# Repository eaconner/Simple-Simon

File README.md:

# Simple Simon Kit #

Red then green...no, blue?...wait!...BUZZ! Remember the classic game of Simon?
Well, here is a build-your-own Simon kit that will sharpen your reaction time while teaching you basic soldering (a useful skill in its own right).

After you have successfully built a working Simon game, you will have a greater knowledge of through-hole soldering and the tools, techniques, and terminology required to populate your own PCB prototype. Additionally, the source code and design files are available, making this project a great entryway into microcontrollers and embedded programming. Game on!

## Parts List ##
|	Qty	|	Part				|	Description				|	Digikey Part #	|
|:-----:|-----------------------|---------------------------|-------------------|
|	1	|	U1					|	Atmel ATtiny45			|	ATTINY45-20PU	|
|	4	|	R1, R2, R3, R4		|	470ohm 1/4w Resistor	|	CF14JT470RCT	|
|	1	|	D1					|	5mm Red LED				|	160-1678		|
|	1	|	D2					|	5mm Green LED			|	160-1677		|
|	1	|	D3					|	5mm Blue LED			|	160-1610		|
|	1	|	D4					|	5mm Yellow LED			|	160-1686		|
|	1	|	SG1					|	12mm Piezo Buzzer		|	102-3752		|
|	5	|	S1, S2, S3, S4, S5	|	Pushbutton				|	450-1644		|
|	1	|	BAT1				|	Battery Holder			|	BS-7			|
|	1	|	BAT1				|	CR2032 Battery			|	P189			|

## Instructions ##
1. Insert the ATtiny45 microcontroller into U1. Make sure the dot in the corner of the chip is aligned with the white silk screen dot on the board. Flip the board over, then solder into place.
2. Insert the (4) four resistors into R1, R2, R3, & R4 by bending the legs down. Flip the board over and solder into place.
3. Insert the (4) four LEDs into D1, D2, D3, & D4. Each LED has a short leg and a long leg. The long leg goes into the hole closest to the edge of the board. Also make sure it sits flush with the PCB. Then solder into place. **Note: You can check the color of the LED by touching the long leg to the "+" side of the CR2032 battery and the short leg to the "-" side.**
4. Insert the buzzer into SG1. Flip the board over and solder into place.
5. Insert the battery holder on the back of the board into BAT1. Flip the board over and solder into place.
6. Insert the battery into the holder.

## Gameplay ##

Press the "Start" button to begin. Memorize and repeat an increasing sequence of colors and tones. In higher levels the game goes faster. If you make a mistake, the correct LED blinks three times and game-over animation is played. If you have beaten the best score, your score is saved and the best-score animation is played.

- If the **red** button is held during when the start button is pressed, the best score is erased.
- If the **green** button is held during when the start button is pressed, starts a random sequence of lights and tones.
- If the **blue** button is held during when the start button is pressed, starts a new game at the highest achieved level.
- If the **yellow** button is held during when the start button is pressed, toggles the sound on or off.

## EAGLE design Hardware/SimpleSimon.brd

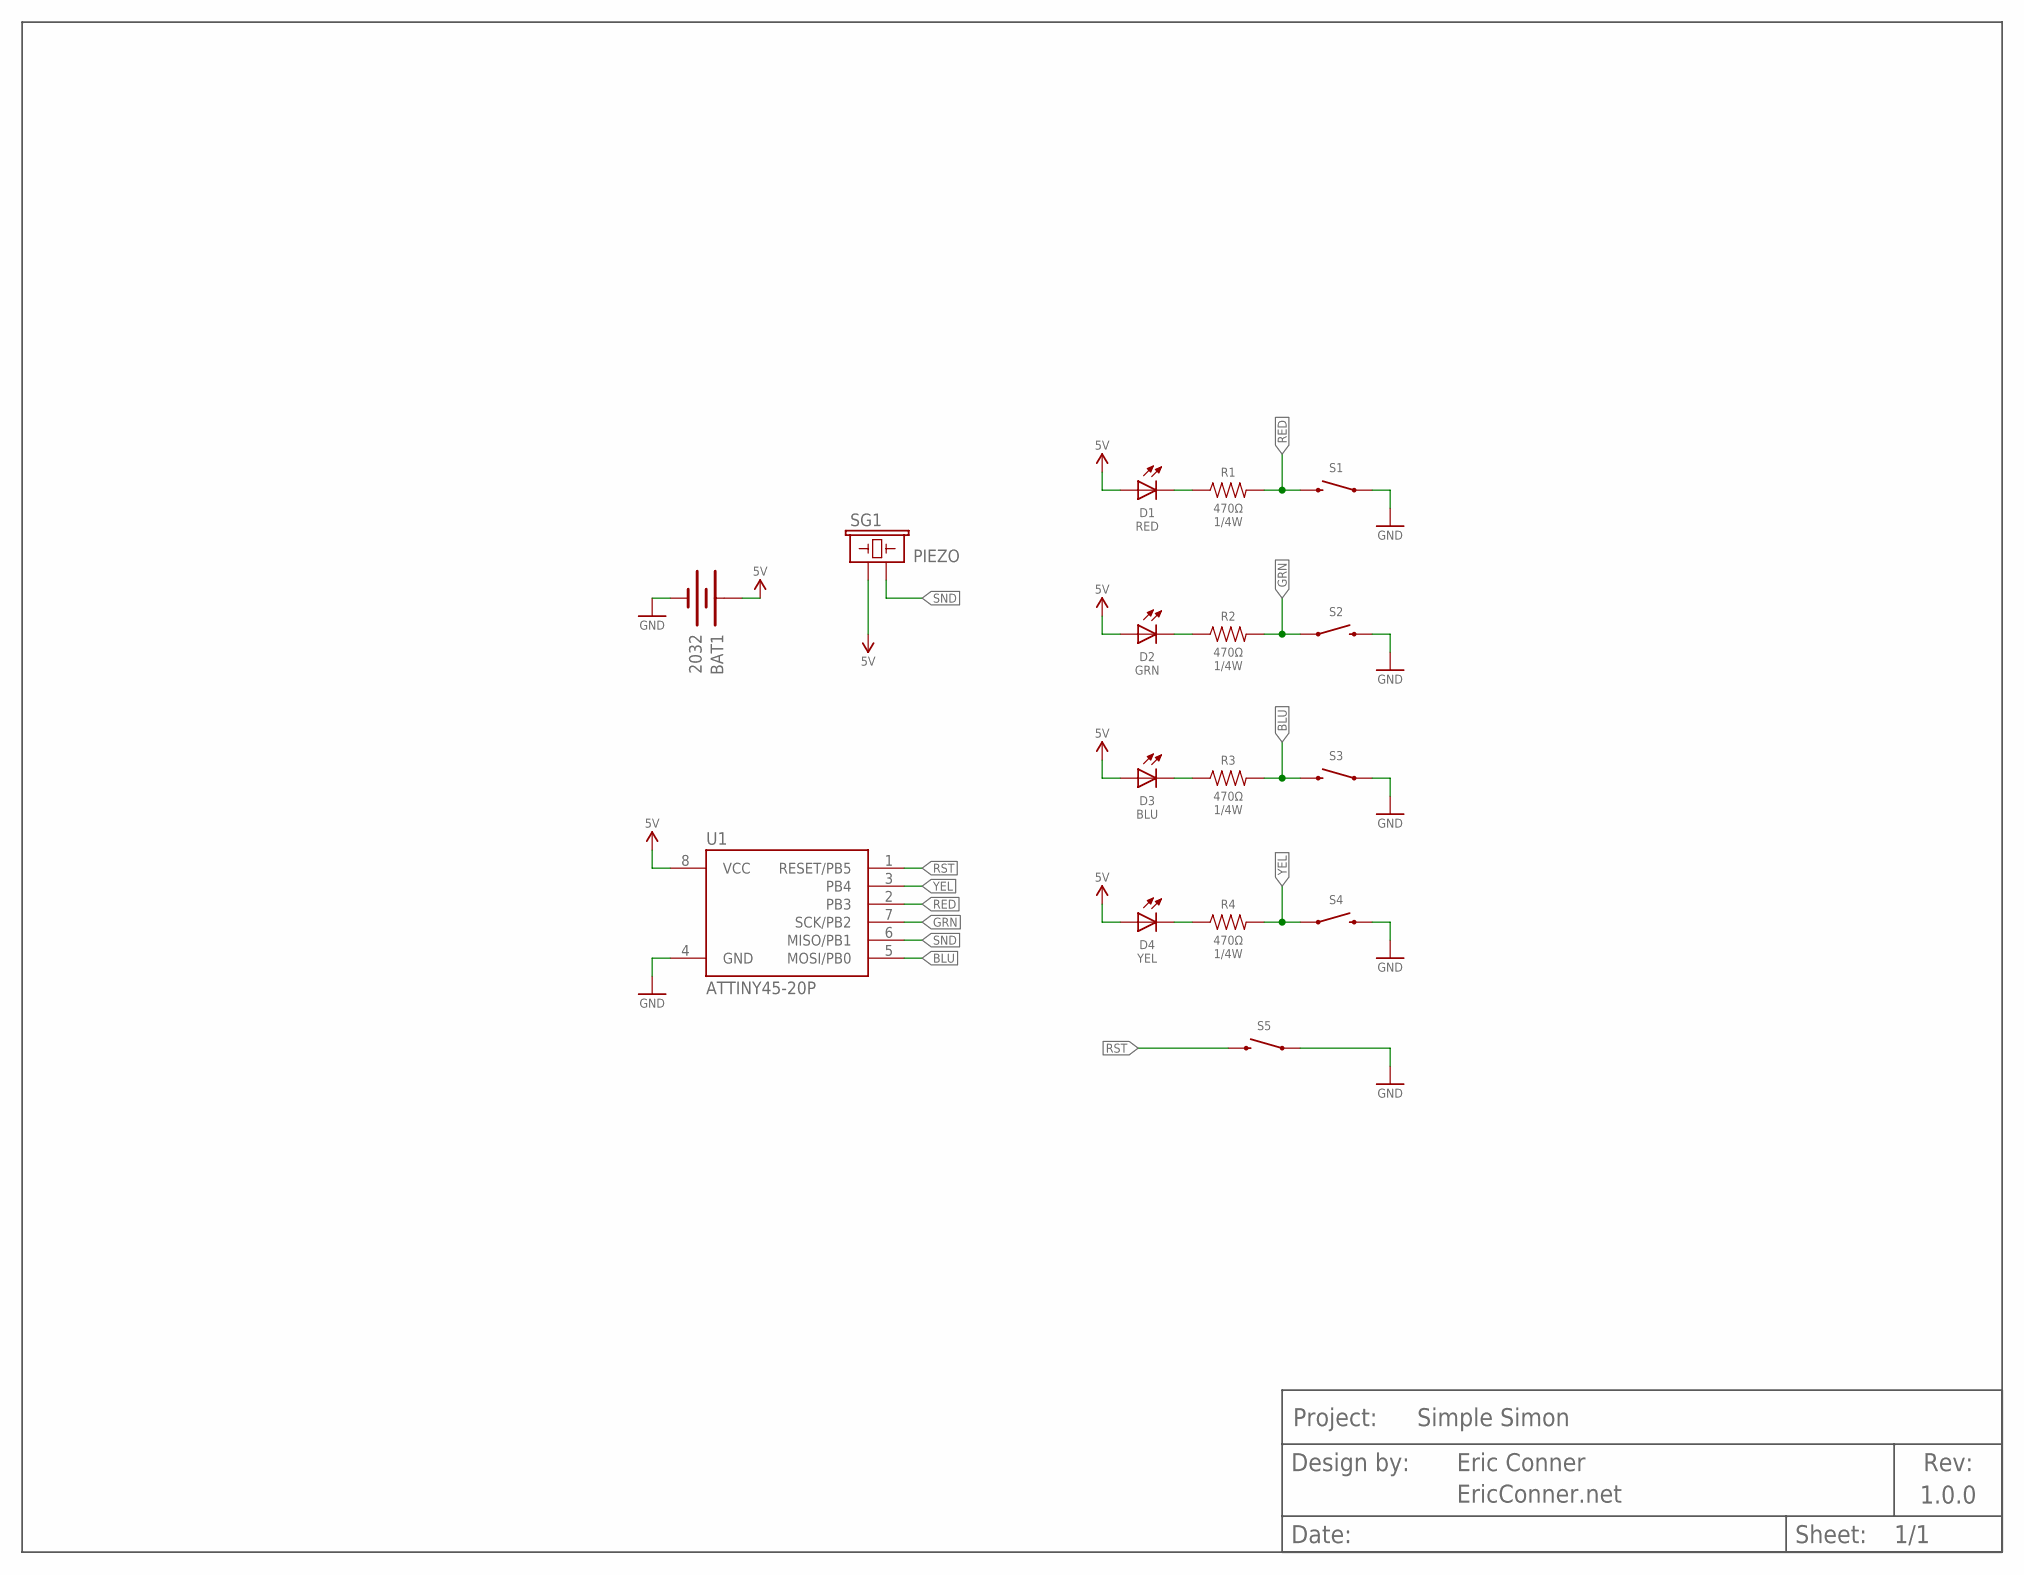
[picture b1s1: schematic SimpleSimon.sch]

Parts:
BAT1: 2032; BAT-2032; DIGIKEY BS-7-ND
BORDER1: BORDER_LETTER-MINIMAL; MINIMAL_LOGO
D1: RED; LED5MM; DIGIKEY 160-1678-ND
D2: GRN; LED5MM; DIGIKEY 160-1677-ND
D3: BLU; LED5MM; DIGIKEY 160-1610-ND
D4: YEL; LED5MM; DIGIKEY 160-1686-ND
R1, R2, R3, R4: 470Ω; 1/4R; DIGIKEY CF14JT470RCT-ND
S1, S2, S3, S4, S5: SWITCH-MOMENTARY-2PTH; TACTILE-PTH; DIGIKEY 450-1644-ND
SG1: PIEZO; BUZZER-12MM; DIGIKEY 102-3752-ND
U1: ATTINY45-20P; PDIP08_300MIL; DIGIKEY ATTINY45-20PU-ND

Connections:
BLU: R3.P$2 (2), S3.3 (2), U1.5 (MOSI/PB0)
GND: BAT1.-, S1.1, S2.3 (2), S3.1, S4.3 (2), S5.1, U1.4 (GND)
GRN: R2.P$2 (2), S2.1, U1.7 (SCK/PB2)
unnamed: D1.K (C), R1.P$1 (1)
unnamed: D2.K (C), R2.P$1 (1)
unnamed: D3.K (C), R3.P$1 (1)
unnamed: D4.K (C), R4.P$1 (1)
RED: R1.P$2 (2), S1.3 (2), U1.2 (PB3)
RST: S5.3 (2), U1.1 (RESET/PB5)
SND: SG1.- (2), U1.6 (MISO/PB1)
VCC: BAT1.+, D1.A, D2.A, D3.A, D4.A, SG1.+ (1), U1.8 (VCC)
YEL: R4.P$2 (2), S4.1, U1.3 (PB4)

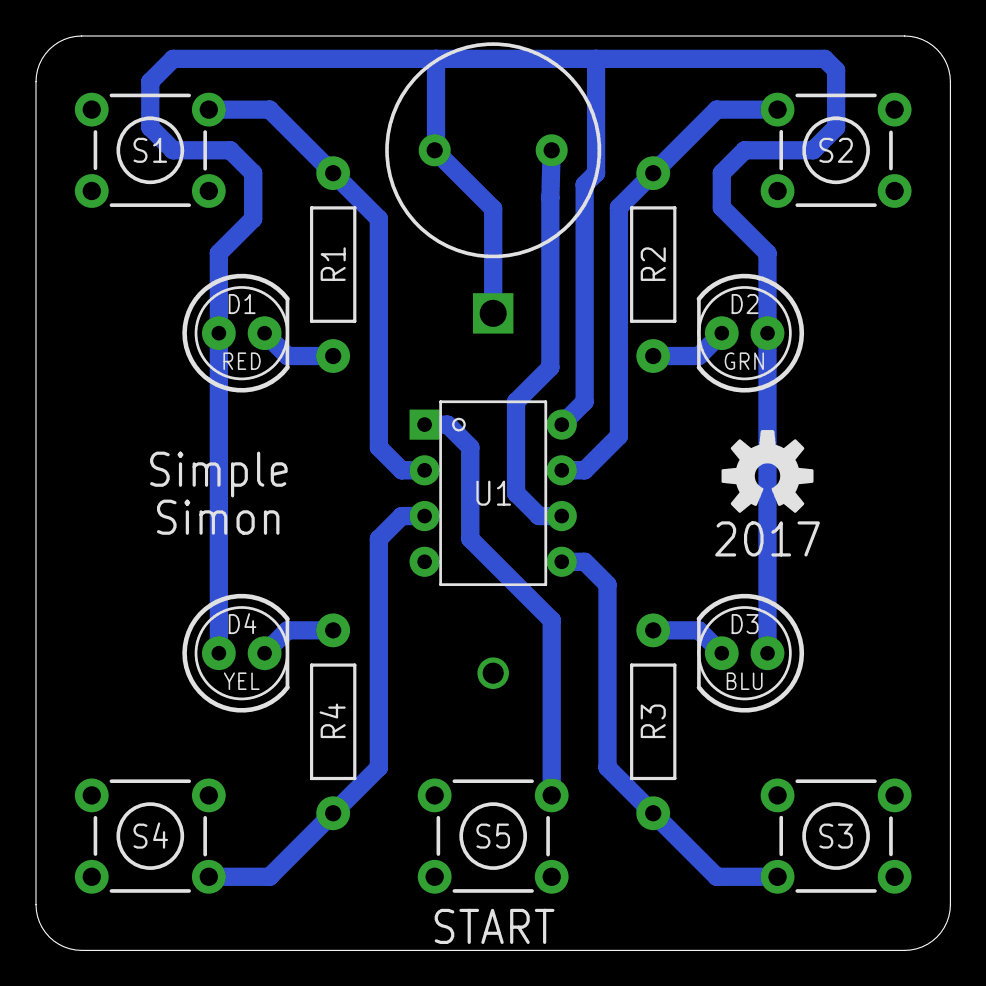
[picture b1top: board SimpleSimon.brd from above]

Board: 2 copper layers, 50.8 x 50.8 mm, 18 parts (1 on the bottom side), 12 nets.

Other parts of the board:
U$1: OSHW-LOGO-M

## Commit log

2020-04-15 Inital Commit

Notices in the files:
parts and their libraries:
SparkFun-Electromechanical: Licensing: Creative Commons ShareAlike 4.0 International - https://creativecommons.org/licenses/by-sa/4.0
SparkFun-Aesthetics: Licensing: CC v3.0 Share-Alike You are welcome to use this library for commercial purposes.
